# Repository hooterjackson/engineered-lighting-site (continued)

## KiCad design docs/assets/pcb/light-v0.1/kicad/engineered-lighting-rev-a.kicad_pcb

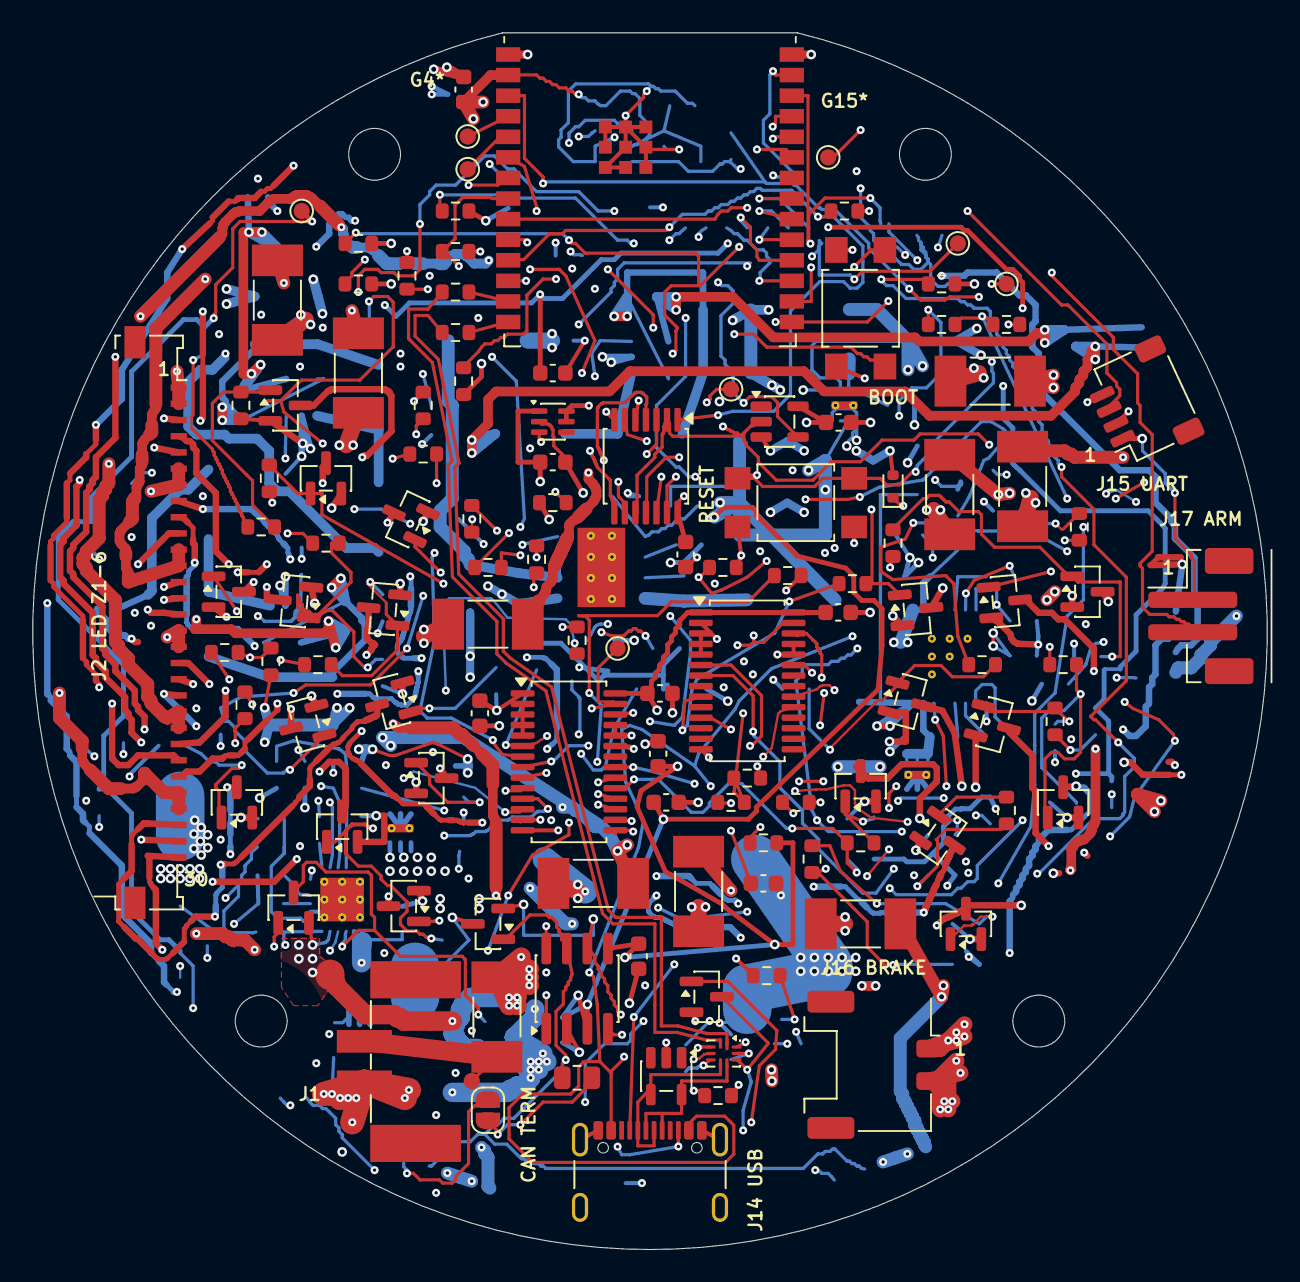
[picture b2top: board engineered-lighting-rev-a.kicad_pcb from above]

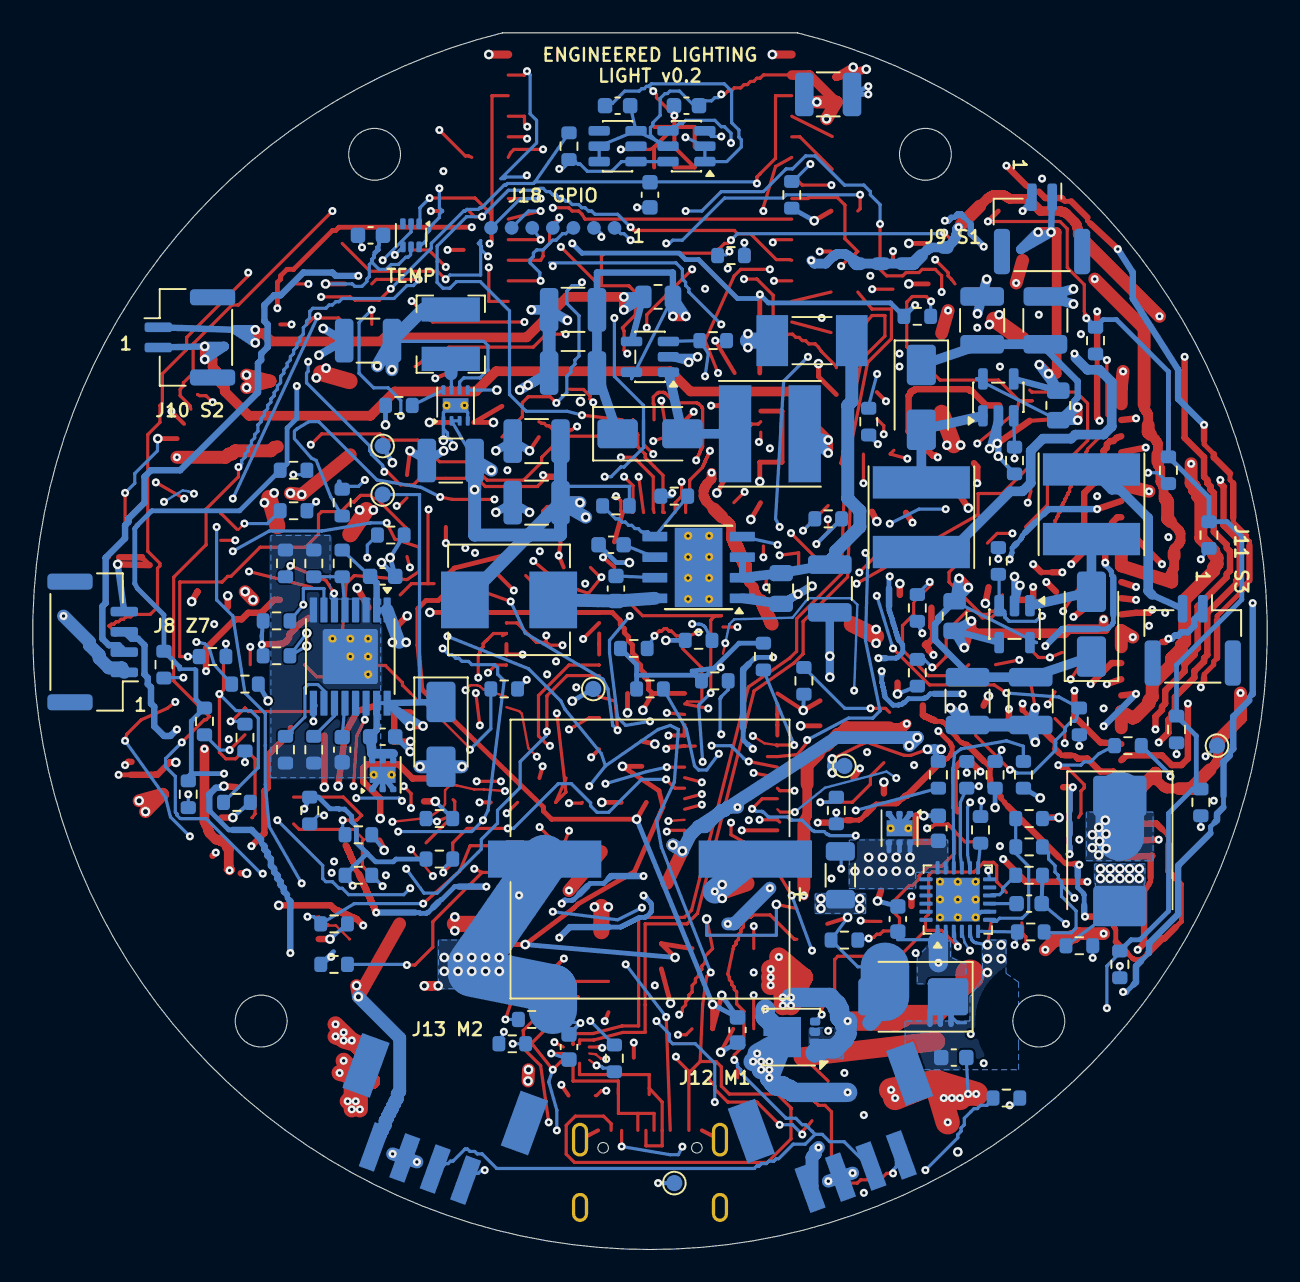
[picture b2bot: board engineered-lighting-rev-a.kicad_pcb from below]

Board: 8 copper layers, 76.2 x 75.1 mm, 264 parts (141 on the bottom side), 163 nets.

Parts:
C1, C22, C42, C43: 1u; C_0603_1608Metric
C2, C4, C5, C20, C21, C30, C31, C40, C41, C44, C45, C46: 100n; C_0603_1608Metric
C3, C510, C511, C512, C513: 22uF 25V X7R; C_1210_3225Metric
C500, C502, C503, C505, C509, C514, C515, C517, C518: 100nF 100V X7R; C_0603_1608Metric
C501: 1uF 100V X7R; C_1206_3216Metric
C504: 1000uF 50V low ESR; CP_CDE_AFK_CaseP_D16_H17_Provisional
C506, C519, C520, C521, C522, C523, C524: 10uF 50V X7R; C_1210_3225Metric
C507: 220nF 50V X7R; C_0805_2012Metric
C508: 1uF 25V X7R; C_0603_1608Metric
C516: 47nF 50V X7R; C_0603_1608Metric
D30: TPD1E10B06DYAR; D_SOD-523
D500: SMBJ33CA 33V bidirectional TVS; D_SMB
D501: 60V output negative transient Schottky; D_SMA
D502, D503, D504: 60V 1A flyback Schottky; D_SMA
D505: 60V 5A output negative transient Schottky; D_SMC
F1: 6.3A backup fuse; Enclosure_F1
F2, F3: 1A motor branch fuse; Fuse_Littelfuse-NANO2-451_453
F4, F5, F6, F7, F8, F9, F10: 0.75A ambient zone fuse; Fuse_Littelfuse-NANO2-451_453
F11: 0.5A logic branch fuse; Fuse_Littelfuse-NANO2-451_453
H1, H2, H3, H4: M3 / 3.2mm NPTH; MountingHole_3.2mm_M3
J1: 24V INPUT; Enclosure_J1
J2: 2005280300 / 6-ZONE FLEX; Molex_2005280300_30P_Central_LED
J8: ZONE 7; JST_GH_BM04B-GHS-TBT_1x04-1MP_P1.25mm_Vertical
J9: SPOT 1; Enclosure_J9
J10: SPOT 2; Enclosure_J10
J11: SPOT 3; JST_GH_BM02B-GHS-TBT_1x02-1MP_P1.25mm_Vertical
J12: MOTOR 1; JST_PA_BM04B_PASS_TFT_1x04_P2mm_Vertical
J13: MOTOR 2; JST_PA_BM04B_PASS_TFT_1x04_P2mm_Vertical
J14: USB DATA /24V REQUIRED; USB_C_Receptacle_GCT_USB4105-xx-A_16P_TopMnt_Horizontal
J15: UART DEBUG; JST_SH_SM04B-SRSS-TB_1x04-1MP_P1.00mm_Horizontal
J16: BRAKE / BUS; Enclosure_J16
J17: ARM SWITCH; Enclosure_J17
J18: GPIO EXPANSION 3V3; Expansion_SolderPads_1x07_P1p27mm
JP1: CAN TERMINATION; SolderJumper-2_P1.3mm_Open_RoundedPad1.0x1.5mm
L500: 22uH 2.5A RMS 5.5A sat; L_Bourns_SRP7050TA
L501: 2.2uH 2.9A RMS 3A sat; L_Bourns-SRN4018
L502, L503, L504: 220uH +/-20%, .6A RMS .7A saturation; L_Bourns_SRN6045
Q30: MMBT3904; SOT-23
Q101, Q102, Q103, Q104, Q105, Q106, Q107, Q108, Q109, Q110, Q111, Q112, Q113, Q114, Q115, Q116, Q117, Q118, Q119, Q120, Q121: AO3422; SOT-23
Q500: 100V reverse blocking MOSFET; VSON-8_3.3x3.3mm_P0.65mm_NexFET
Q501: fast reverse gate pull-down; SOT-23
R1, R2, R3, R4, R5, R6, R20, R21, R36, R40, R41, R502, R504, R506, R507, R508, R509, R512, R513, R518, R519, R520: 10k; R_0603_1608Metric
R7, R8, R301, R302, R303, R304, R305, R306, R307, R308, R309, R310, R311, R312, R313, R314, R315, R316, R317, R318, R319, R320, R321: 2.2k; R_0603_1608Metric
R9, R10, R11, R34, R35, R201, R202, R203, R204, R205, R206, R207, R208, R209, R210, R211, R212, R213, R214, R215, R216, R217, R218, R219, R220, R221, R510: 100k; R_0603_1608Metric
R22: 120; R_0805_2012Metric
R30, R31: 5.1k; R_0603_1608Metric
R32, R33: 0; R_0603_1608Metric
R37, R38, R42: 1k; R_0603_1608Metric
R39: 33k; R_0603_1608Metric
R101, R102, R103, R104, R105, R106, R107, R108, R109, R110, R111, R112, R113, R114, R115, R116, R117, R118, R119, R120, R121: 220; R_0603_1608Metric
R500: 4.02k; R_0603_1608Metric
R501: 140k; R_0603_1608Metric
R503, R517: 210k; R_0603_1608Metric
R505: 165k; R_0603_1608Metric
R511: 24.9k; R_0603_1608Metric
R514: 4.7k; R_0603_1608Metric
R515: 24.3k; R_0603_1608Metric
R516: 402k; R_0603_1608Metric
R521: 47k; R_0603_1608Metric
R523, R524, R525: 0.300ohm 1% 0.125W; R_0805_2012Metric
R526, R527, R528: 910; R_0603_1608Metric
S1: RESET; SW_SPST_TL3305A
S2: BOOT; SW_SPST_TL3305A
TP1: GND; TestPoint_Pad_D1.0mm
TP2: VIN24_RAW; TestPoint_Pad_D1mm_NoComponentCourtyard
TP3: V24_BUS; TestPoint_Pad_D1.0mm
TP4: +5V; TestPoint_Pad_D1.0mm
TP5: +3V3; TestPoint_Pad_D1.0mm
TP6: GATE_BIAS; TestPoint_Pad_D1.0mm
TP7: LIGHT_ENABLE_SAFE; TestPoint_Pad_D1.0mm
TP8: EFUSE_RESET_N; TestPoint_Pad_D1.0mm
TP9: V24_SPOT; TestPoint_Pad_D1.0mm
TP10: I2C_SDA; TestPoint_Pad_D1.0mm
TP11: I2C_SCL; TestPoint_Pad_D1.0mm
TP12: PCA_OE; TestPoint_Pad_D1.0mm
TP13: GPIO4 STRAP; TestPoint_Pad_D1.0mm
TP14: GPIO5 STRAP; TestPoint_Pad_D1.0mm
TP15: GPIO15 STRAP; TestPoint_Pad_D1.0mm
U1: ESP32-C6-WROOM-1-N8; ESP32-C6-WROOM-1
U2, U3: PCA9685PW,118; TSSOP-28_4.4x9.7mm_P0.65mm
U4: TCAN1042HGVDRQ1; SOIC-8_3.9x4.9mm_P1.27mm
U5: 74HCS08PWJ; TSSOP-14_4.4x5mm_P0.65mm
U6: SN74LVC1G04DBVR; SOT-23-5
U7, U8, U9: 333mA spotlight CC driver; TSOT-23-5
U10: 24V to 5V 1A buck; TI_DDA0008B_EP2.71x3.4_ThermalVias_125um
U11: 5V to 3.3V 1A fixed buck; Texas_DSG0008A_WSON-8-1EP_2x2mm_P0.5mm_EP0.9x1.6mm_ThermalV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
U12: 24V input eFuse / 4.5A nominal; Texas_RGE0024H_VQFN-24-1EP_4x4mm_P0.5mm_EP2.7x2.7mm_Thermal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
U13: switched ambient gate bias; SOT-363_SC-70-6
U14: spot branch gated eFuse 0.494A nominal; TI_PWP0016A_EP3.3x3.3_6ThermalVias_125um
U15: ESDS302; SOT-23-5
U16: NUP2105LT1G; SOT-23
U17: TMUXHS221F; TI_RSW0010A_UQFN10_1p4x1p8_TMUXHS221F
U18: TPS3808G33; SOT-23-6_FabPin1
U19: SN74LVC1G97 AND Schmitt; SOT-23-6
U20: TMP112AIDRLR; SOT-563
U500, U501: 27V flat-clamp transient protector; WSON-6-1EP_2x2mm_P0.65mm_EP1x1.6mm_ThermalVias

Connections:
+3V3: C2.1, C3.1, C4.1, C5.1, C21.1, C40.1, C41.1, C42.1, C43.1, C44.1, C45.1, C46.1, C513.1, C514.1, J15.1, J17.1, J18.1, L501.2, R1.1, R2.1, R3.1, R6.2, R7.2, R8.2, R20.2, R36.2, R508.1, R509.1, R512.1, R513.1, R520.1, TP5.1, U1.2, U2.28, U3.1, U3.28, U4.5, U5.14, U6.5, U11.6, U13.1, U18.3, U18.5, U18.6, U19.5, U20.5
+5V: C20.1, C22.1, C510.1, C511.1, C512.1, L500.2, R510.1, TP4.1, U4.3, U11.2, U11.3
ARM: J17.2, R5.1, U5.13
BOOT_GPIO8: R3.2, U1.10
BOOT_GPIO9: R2.2, S2.1, U1.15
BUCK3_PGOOD: R513.2, U11.8
BUCK3_SW: L501.1, U11.7
BUCK5_BOOT: C509.1, U10.7
BUCK5_FB: R510.2, R511.1, U10.5
BUCK5_PGOOD: R512.2, U10.4
BUCK5_SW: C509.2, L500.1, U10.8
BUCK5_VCC: C508.1, U10.6
CAN_H: J12.3, J13.3, R22.1, U4.7, U16.1
CAN_L: J12.4, J13.4, JP1.2, U4.6, U16.2
CAN_RX: U1.7, U4.4
CAN_STB: R21.1, U4.8
CAN_TERM: JP1.1, R22.2
CAN_TX: R20.1, U1.6, U4.1
EFUSE_BGATE: Q500.4, Q501.3, U12.3
EFUSE_DRV: Q501.1, U12.4
EFUSE_DVDT: C503.1, U12.9
EFUSE_FLT_N: R508.2, U12.14
EFUSE_ILIM: R500.1, U12.10
EFUSE_IMON: R507.1, U12.13
EFUSE_OVP: R503.2, R504.1, U12.7
EFUSE_PGOOD: R509.2, U12.16
EFUSE_PGTH: R505.2, R506.1, U12.15
EFUSE_RESET_N: TP8.1, U12.12
EFUSE_UVLO: R501.2, R502.1, U12.6
GATE_01: Q101.1, R101.2, R201.1
GATE_02: Q102.1, R102.2, R202.1
GATE_03: Q103.1, R103.2, R203.1
GATE_04: Q104.1, R104.2, R204.1
GATE_05: Q105.1, R105.2, R205.1
GATE_06: Q106.1, R106.2, R206.1
GATE_07: Q107.1, R107.2, R207.1
GATE_08: Q108.1, R108.2, R208.1
GATE_09: Q109.1, R109.2, R209.1
GATE_10: Q110.1, R110.2, R210.1
GATE_11: Q111.1, R111.2, R211.1
GATE_12: Q112.1, R112.2, R212.1
GATE_13: Q113.1, R113.2, R213.1
GATE_14: Q114.1, R114.2, R214.1
GATE_15: Q115.1, R115.2, R215.1
GATE_16: Q116.1, R116.2, R216.1
GATE_17: Q117.1, R117.2, R217.1
GATE_18: Q118.1, R118.2, R218.1
GATE_19: Q119.1, R119.2, R219.1
GATE_20: Q120.1, R120.2, R220.1
GATE_21: Q121.1, R121.2, R221.1
GATE_BIAS: C515.1, R301.1, R302.1, R303.1, R304.1, R305.1, R306.1, R307.1, R308.1, R309.1, R310.1, R311.1, R312.1, R313.1, R314.1, R315.1, R316.1, R317.1, R318.1, R319.1, R320.1, R321.1, TP6.1, U13.5, U13.6
GND: C1.2, C2.2, C3.2, C4.2, C5.2, C20.2, C21.2, C22.2, C30.2, C31.2, C40.2, C41.2, C42.2, C43.2, C44.2, C45.2, C46.2, C500.2, C501.2, C502.2, C503.2, C504.2, C505.2, C506.2, C507.2, C508.2, C510.2, C511.2, C512.2, C513.2, C514.2, C515.2, C517.2, C518.2, C519.2, C520.2, C521.2, C522.2, C523.2, C524.2, D30.2, D500.2, D501.2, D505.2, J1.2, J12.2, J13.2, J14.A1, J14.A12, J14.B1, J14.B12, J14.SH, J15.2, J16.2, J18.2, Q30.2, Q101.2, Q102.2, Q103.2, Q104.2, Q105.2, Q106.2, Q107.2, Q108.2, Q109.2, Q110.2, Q111.2, Q112.2, Q113.2, Q114.2, Q115.2, Q116.2, Q117.2, Q118.2, Q119.2, Q120.2, Q121.2, R4.2, R5.2, R9.2, R10.2, R11.2, R21.2, R30.2, R31.2, R35.2, R37.2, R38.2, R39.2, R40.2, R201.2, R202.2, R203.2, R204.2, R205.2, R206.2, R207.2, R208.2, R209.2, R210.2, R211.2, R212.2, R213.2, R214.2, R215.2, R216.2, R217.2, R218.2, R219.2, R220.2, R221.2, R500.2, R502.2, R504.2, R506.2, R507.2, R511.2, R514.2, R521.2, R526.2, R527.2, R528.2, S1.2, S2.2, TP1.1, U1.1, U1.28, U1.29, U2.1, U2.2, U2.3, U2.4, U2.5, U2.14, U2.24, U2.25, U3.2, U3.3, U3.4, U3.5, U3.14, U3.24, U3.25, U4.2, U5.7, U6.3, U7.2, U8.2, U9.2, U10.1, U10.9, U11.1, U11.4, U11.5, U11.9, U12.8, U12.25, U13.2, U14.9, U15.2, U16.3, U17.3, U18.2, U19.1, U19.2, U20.2, U20.4, U500.1, U500.2, U500.3, U500.7, U501.1, U501.2, U501.3, U501.7
GPIO4_STRAP: TP13.1, U1.4
GPIO5_STRAP: TP14.1, U1.5
GPIO15_STRAP: TP15.1, U1.23
GPIO19: J18.3, U1.17
GPIO20: J18.4, U1.18
GPIO21: J18.5, U1.19
GPIO22: J18.6, U1.20
GPIO23: J18.7, U1.21
I2C_SCL: R8.1, TP11.1, U1.26, U2.26, U3.26, U20.1
I2C_SDA: R7.1, TP10.1, U1.27, U2.27, U3.27, U20.6
LIGHT_ENABLE: R4.1, U1.8, U5.12
LIGHT_ENABLE_SAFE: R514.1, TP7.1, U5.2, U5.5, U5.10, U6.2, U13.3, U14.7, U19.4
LIGHT_REQUEST_ARMED: U5.11, U19.3
MCU_EN: C1.1, R1.2, R42.2, S1.1, U1.3
PCA_OE: R6.1, TP12.1, U2.23, U3.23, U6.4
PWM_01: R101.1, R301.2, U2.6
PWM_02: R102.1, R302.2, U2.7
PWM_03: R103.1, R303.2, U2.8
PWM_04: R104.1, R304.2, U2.9
PWM_05: R105.1, R305.2, U2.10
PWM_06: R106.1, R306.2, U2.11
PWM_07: R107.1, R307.2, U2.12
PWM_08: R108.1, R308.2, U2.13
PWM_09: R109.1, R309.2, U2.15
PWM_10: R110.1, R310.2, U2.16
PWM_11: R111.1, R311.2, U2.17
PWM_12: R112.1, R312.2, U2.18
PWM_13: R113.1, R313.2, U2.19
PWM_14: R114.1, R314.2, U2.20
PWM_15: R115.1, R315.2, U2.21
PWM_16: R116.1, R316.2, U3.6
PWM_17: R117.1, R317.2, U3.7
PWM_18: R118.1, R318.2, U3.20
PWM_19: R119.1, R319.2, U3.9
PWM_20: R120.1, R320.2, U3.19
PWM_21: R121.1, R321.2, U3.11
READY_3V3: R41.1, R42.1, U18.1, U19.6
SPOT1_CTRL: R526.1, U5.3, U7.3
SPOT1_LED_MINUS: J9.2, L502.1
SPOT1_LED_PLUS: J9.1, R523.2, U7.4
SPOT1_PWM: R9.1, U1.11, U5.1
SPOT1_SW: D502.2, L502.2, U7.1
SPOT2_CTRL: R527.1, U5.6, U8.3
SPOT2_LED_MINUS: J10.2, L503.1
SPOT2_LED_PLUS: J10.1, R524.2, U8.4
SPOT2_PWM: R10.1, U1.12, U5.4
SPOT2_SW: D503.2, L503.2, U8.1
SPOT3_CTRL: R528.1, U5.8, U9.3
SPOT3_LED_MINUS: J11.2, L504.1
SPOT3_LED_PLUS: J11.1, R525.2, U9.4
SPOT3_PWM: R11.1, U1.16, U5.9
SPOT3_SW: D504.2, L504.2, U9.1
SPOT_EFUSE_DVDT: C516.1, U14.12
SPOT_EFUSE_FLT_N: R520.2, U14.14
SPOT_EFUSE_ILIM: R515.1, U14.11
SPOT_EFUSE_IMON: R519.1, U14.10
SPOT_EFUSE_MODE: R516.1, U14.6
SPOT_EFUSE_OVP: R517.2, R518.1, U14.5
SPOT_RTN: C516.2, R515.2, R516.2, R518.2, R519.2, U14.3, U14.8, U14.17
UART_RX: J15.4, U1.24
UART_TX: J15.3, U1.25
USB_CC1: J14.A5, R30.1
USB_CC2: J14.B5, R31.1
USB_DM: R32.1, U17.2
USB_DM_HOST: J14.A7, J14.B7, U15.4, U17.6
USB_DM_MCU: R32.2, U1.13
USB_DM_PARK: R38.1, U17.4
USB_DP: R33.1, U17.1
USB_DP_HOST: J14.A6, J14.B6, U15.5, U17.7
USB_DP_MCU: R33.2, U1.14
USB_DP_PARK: R37.1, U17.5
USB_PRESENT_N: Q30.3, R36.1, U1.9, U17.8
USB_READY_SELECT: R39.1, R41.2, U17.10
USB_SENSE_BASE: Q30.1, R34.2, R35.1
USB_VBUS: C30.1, C31.1, D30.1, J14.A4, J14.A9, J14.B4, J14.B9, R34.1, R40.1, U17.9
V24_BUS: C504.1, C505.1, C517.1, D505.1, F2.1, F3.1, F4.1, F5.1, F6.1, F7.1, F8.1, F9.1, F10.1, F11.1, J16.1, R505.1, R517.1, TP3.1, U12.17, U12.18, U14.1, U14.2, U501.4, U501.5, U501.6
V24_LOGIC: C506.1, C507.1, F11.2, U10.2, U10.3
V24_MOTOR1: F2.2, J12.1
V24_MOTOR2: F3.2, J13.1
V24_SPOT: C518.1, C519.1, C520.1, C521.1, C522.1, C523.1, C524.1, D501.1, D502.1, D503.1, D504.1, R521.1, R523.1, R524.1, R525.1, TP9.1, U7.5, U8.5, U9.5, U14.15, U14.16, U500.4, U500.5, U500.6
VIN24_FUSED: C500.1, C501.1, D500.1, F1.2, Q500.1, Q500.2, Q500.3, Q501.2, R501.1, R503.1, U12.5
VIN24_RAW: F1.1, J1.1, TP2.1
VIN24_RPP: C502.1, Q500.5, U12.1, U12.2
ZONE1_24V: F4.2, J2.16, J2.17
ZONE1_C: J2.20, Q103.3
ZONE1_N: J2.19, Q102.3
ZONE1_W: J2.18, Q101.3
ZONE2_24V: F5.2, J2.21, J2.22
ZONE2_C: J2.25, Q106.3
ZONE2_N: J2.24, Q105.3
ZONE2_W: J2.23, Q104.3
ZONE3_24V: F6.2, J2.26, J2.27
ZONE3_C: J2.30, Q109.3
ZONE3_N: J2.29, Q108.3
ZONE3_W: J2.28, Q107.3
ZONE4_24V: F7.2, J2.1, J2.2
ZONE4_C: J2.5, Q112.3
ZONE4_N: J2.4, Q111.3
ZONE4_W: J2.3, Q110.3
ZONE5_24V: F8.2, J2.6, J2.7
ZONE5_C: J2.10, Q115.3
ZONE5_N: J2.9, Q114.3
ZONE5_W: J2.8, Q113.3
ZONE6_24V: F9.2, J2.11, J2.12
ZONE6_C: J2.15, Q118.3
ZONE6_N: J2.14, Q117.3
ZONE6_W: J2.13, Q116.3
ZONE7_24V: F10.2, J8.1
ZONE7_C: J8.4, Q121.3
ZONE7_N: J8.3, Q120.3
ZONE7_W: J8.2, Q119.3

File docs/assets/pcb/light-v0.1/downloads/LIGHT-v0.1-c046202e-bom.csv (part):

"Item","Designators","Quantity per board","Quantity for 2 prototypes (no attrition)","Value / description","Manufacturer","Manufacturer part number","KiCad footprint","Primary source","Source revision / context","Assembly / engineering note","Sourcing evidence URL","Order status"
"1","U1","1","2","ESP32-C6-WROOM-1-N8","Espressif","ESP32-C6-WROOM-1-N8","EL:ESP32-C6-WROOM-1","https://documentation.espressif.com/esp32-c6-wroom-1_wroom-1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","v1.4; module pad29 and land pattern independently inspected","3.3V supply; antenna keepout and peak-current/decoupling verification required","https://documentation.espressif.com/esp32-c6-wroom-1_wroom-1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","QUOTE ONLY - exact source/quantity/process not confirmed"
"2","R1, R2, R3, R4, R5, R6, R20, R21, R36, R40, R41, R502, R504, R506, R507, R508, R509, R512, R513, R518, R519, R520, R526, R527, R528","25","50","10k","Yageo","RC0603FR-0710KL","Resistor_SMD:R_0603_1608Metric","https://www.yageogroup.com/component-documentation/download/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","Exact manufacturer specsheet; dynamically generated2026, access2026-09-06","0.1W0603 or0.125W0805 at70C; exact value/code checked; assembler must confirm available quantity","https://www.yageogroup.com/component-documentation/download/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","QUOTE ONLY - exact source/quantity/process not confirmed"
"3","C1, C22, C42, C43, C508","5","10","1u / 1uF 25V X7R","TDK","C1608X7R1E105K080AB","Capacitor_SMD:C_0603_1608Metric","https://product.tdk.com/en/search/capacitor/ceramic/mlcc/inf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","undated product page; source and stock dates distinguished","","https://product.tdk.com/en/search/capacitor/ceramic/mlcc/inf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","QUOTE ONLY - exact source/quantity/process not confirmed"
"4","R7, R8, R301, R302, R303, R304, R305, R306, R307, R308, R309, R310, R311, R312, R313, R314, R315, R316, R317, R318, R319, R320, R321","23","46","2.2k","Yageo","RC0603FR-072K2L","Resistor_SMD:R_0603_1608Metric","https://www.yageogroup.com/component-documentation/download/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","Exact manufacturer specsheet; dynamically generated2026, access2026-09-06","0.1W0603 or0.125W0805 at70C; exact value/code checked; assembler must confirm available quantity","https://www.yageogroup.com/component-documentation/download/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","QUOTE ONLY - exact source/quantity/process not confirmed"
"5","R9, R10, R11, R34, R35, R201, R202, R203, R204, R205, R206, R207, R208, R209, R210, R211, R212, R213, R214, R215, R216, R217, R218, R219, R220, R221, R510","27","54","100k","Yageo","RC0603FR-07100KL","Resistor_SMD:R_0603_1608Metric","https://www.yageogroup.com/component-documentation/download/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","Exact manufacturer specsheet; dynamically generated2026, access2026-09-06","0.1W0603 or0.125W0805 at70C; exact value/code checked; assembler must confirm available quantity","https://www.yageogroup.com/component-documentation/download/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","QUOTE ONLY - exact source/quantity/process not confirmed"
"6","C2, C4, C5, C20, C21, C30, C31, C40, C41, C44, C45, C46, C500, C502, C503, C505, C509, C514, C515, C517, C518","21","42","100n / 100nF 100V X7R","Murata","GRM188R72A104KA35D","Capacitor_SMD:C_0603_1608Metric","https://www.murata.com/products/productdetail?partno=GRM188R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","undated exact product page","","https://www.murata.com/products/productdetail?partno=GRM188R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","QUOTE ONLY - exact source/quantity/process not confirmed"
"7","C3, C510, C511, C512, C513","5","10","22uF 25V X7R","Murata","GRM32ER71E226KE15L","Capacitor_SMD:C_1210_3225Metric","https://search.murata.co.jp/Ceramy/image/img/A01X/G101/ENG/G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","-01, 2016-03-07","Nominal voltage/package checked; exact DC-bias effective capacitance and temperature/tolerance still required","https://search.murata.co.jp/Ceramy/image/img/A01X/G101/ENG/G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","QUOTE ONLY - exact source/quantity/process not confirmed"
"8","S1, S2","2","4","RESET / BOOT","E-Switch","TL3305AF160QG","Button_Switch_SMD:SW_SPST_TL3305A","https://www.e-switch.com/wp-content/uploads/2023/01/TL3305.pdf","2022-09-28 family catalog; exact OPN distributor listing","50mA12V; operating temperature -20 to70C; momentary reset/boot","https://www.e-switch.com/wp-content/uploads/2023/01/TL3305.pdf","QUOTE ONLY - exact source/quantity/process not confirmed"
"9","J17","1","2","ARM SWITCH","JST","B2B-PH-SM4-TB(LF)(SN)","ELF:Enclosure_J17","https://www.jst-mfg.com/product/pdf/eng/ePH.pdf","Public manufacturer data reviewed 2026-09-06; exact stock/quotation unconfirmed","JST PH vertical SMD ARM connector, public PH catalogue p2 land pattern. Contact 1 3V3, contact 2 ARM.","https://www.jst-mfg.com/product/pdf/eng/ePH.pdf","QUOTE ONLY - exact source/quantity/process not confirmed"
"10","J15","1","2","UART DEBUG","JST","SM04B-SRSS-TB(LF)(SN)","Connector_JST:JST_SH_SM04B-SRSS-TB_1x04-1MP_P1.00mm_Horizontal","https://www.jst-mfg.com/product/pdf/eng/eSH.pdf","SH catalog p1-3; exact OPN and land drawing visually reviewed","3.3V UART service; SH housing/crimp required; external adapter must not drive power pin1","https://www.jst-mfg.com/product/pdf/eng/eSH.pdf","QUOTE ONLY - exact source/quantity/process not confirmed"
"11","U5","1","2","SN74LVC08APWR","Texas Instruments","SN74LVC08APWR","Package_SO:TSSOP-14_4.4x5mm_P0.65mm","https://www.ti.com/lit/ds/symlink/sn74lvc08a.pdf","Primary pin functions and operating limits reviewed","3.3V quad AND; three PWM gates and physical ARM interlock","https://www.ti.com/lit/ds/symlink/sn74lvc08a.pdf","QUOTE ONLY - exact source/quantity/process not confirmed"
"12","U6","1","2","SN74LVC1G04DBVR","Texas Instruments","SN74LVC1G04DBVR","Package_TO_SOT_SMD:SOT-23-5","https://www.ti.com/lit/ds/symlink/sn74lvc1g04.pdf","Primary pin functions and operating limits reviewed","3.3V inverter driving PCA OE; default-high OE pullup","https://www.ti.com/lit/ds/symlink/sn74lvc1g04.pdf","QUOTE ONLY - exact source/quantity/process not confirmed"
"13","U4","1","2","TCAN1042HGVDRQ1","Texas Instruments","TCAN1042HGVDRQ1","Package_SO:SOIC-8_3.9x4.9mm_P1.27mm","https://www.ti.com/lit/ds/symlink/tcan1042h-q1.pdf","Primary device/pin functions reviewed","5V VCC/3.3V VIO; device bus-fault rating does not rate the complete terminated/protected port","https://www.ti.com/lit/ds/symlink/tcan1042h-q1.pdf","QUOTE ONLY - exact source/quantity/process not confirmed"
"14","U16","1","2","NUP2105LT1G","onsemi","NUP2105LT1G","Package_TO_SOT_SMD:SOT-23","https://www.onsemi.com/download/data-sheet/pdf/nup2105l-d.pdf","NUP2105L/D Rev12 June2026","24V working standoff; transient clamp only; no complete-port continuous high-voltage fault guarantee","https://www.onsemi.com/download/data-sheet/pdf/nup2105l-d.pdf","QUOTE ONLY - exact source/quantity/process not confirmed"
"15","R22","1","2","120","Yageo","RC0805FR-07120RL","Resistor_SMD:R_0805_2012Metric","https://www.yageogroup.com/component-documentation/download/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","Exact manufacturer specsheet; dynamically generated2026, access2026-09-06","0.1W0603 or0.125W0805 at70C; exact value/code checked; assembler must confirm available quantity; termination0.125W, no24V across120ohm fault-survival claim","https://www.yageogroup.com/component-documentation/download/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","QUOTE ONLY - exact source/quantity/process not confirmed"
"16","J14","1","2","USB DATA /24V REQUIRED","GCT","USB4105-GF-A","Connector_USB:USB_C_Receptacle_GCT_USB4105-xx-A_16P_TopMnt_Horizontal","https://gct.co/files/drawings/usb4105.pdf","Drawing B4 2023-12-18 visually checked; relevant lands/body match native and B3","USB data only,24V external power required; connector high-power headline does not rate this board","https://gct.co/files/drawings/usb4105.pdf","QUOTE ONLY - exact source/quantity/process not confirmed"
"17","R30, R31","2","4","5.1k","Yageo","RC0603FR-075K1L","Resistor_SMD:R_0603_1608Metric","https://www.yageogroup.com/component-documentation/download/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","Exact manufacturer specsheet; dynamically generated2026, access2026-09-06","0.1W0603 or0.125W0805 at70C; exact value/code checked; assembler must confirm available quantity","https://www.yageogroup.com/component-documentation/download/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","QUOTE ONLY - exact source/quantity/process not confirmed"
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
